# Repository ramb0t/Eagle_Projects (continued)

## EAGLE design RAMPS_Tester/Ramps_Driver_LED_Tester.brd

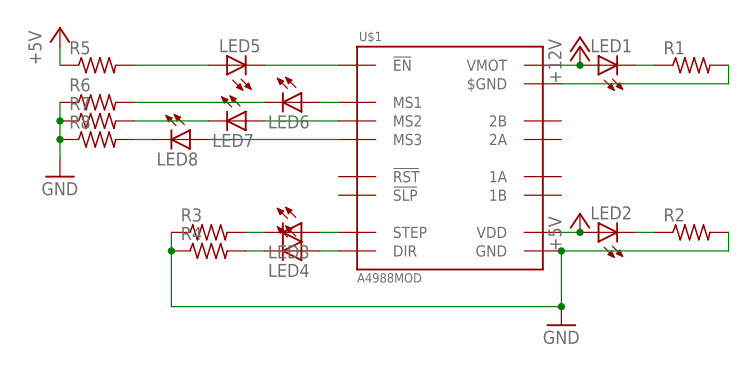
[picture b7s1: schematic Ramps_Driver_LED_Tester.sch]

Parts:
LED1, LED2, LED3, LED4, LED5, LED6, LED7, LED8: LEDCHIPLED_0805; CHIPLED_0805
R1, R2, R3, R4, R5, R6, R7, R8: R-US_R0805; R0805
U$1: A4988MOD

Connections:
+5V: LED2.A, R5.1, U$1.P$10 (VDD)
+12V: LED1.A, U$1.P$16 (VMOT)
GND: R2.2, R3.1, R4.1, R6.1, R7.1, R8.1, U$1.P$9 (GND)
unnamed: LED1.C, R1.1
unnamed: LED2.C, R2.1
unnamed: LED3.A, U$1.P$7 (STEP)
unnamed: LED4.A, U$1.P$8 (DIR)
unnamed: LED3.C, R3.2
unnamed: LED4.C, R4.2
unnamed: LED5.C, U$1.P$1 (!EN)
unnamed: LED5.A, R5.2
unnamed: LED6.A, U$1.P$2 (MS1)
unnamed: LED8.A, U$1.P$4 (MS3)
unnamed: LED7.A, U$1.P$3 (MS2)
unnamed: LED6.C, R6.2
unnamed: LED7.C, R7.2
unnamed: LED8.C, R8.2
unnamed: R1.2, U$1.P$15 ($GND)

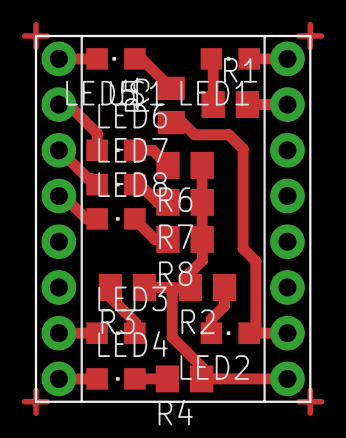
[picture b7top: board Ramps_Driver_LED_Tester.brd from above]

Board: 2 copper layers, 15.2 x 20.3 mm, 17 parts (0 on the bottom side), 18 nets.

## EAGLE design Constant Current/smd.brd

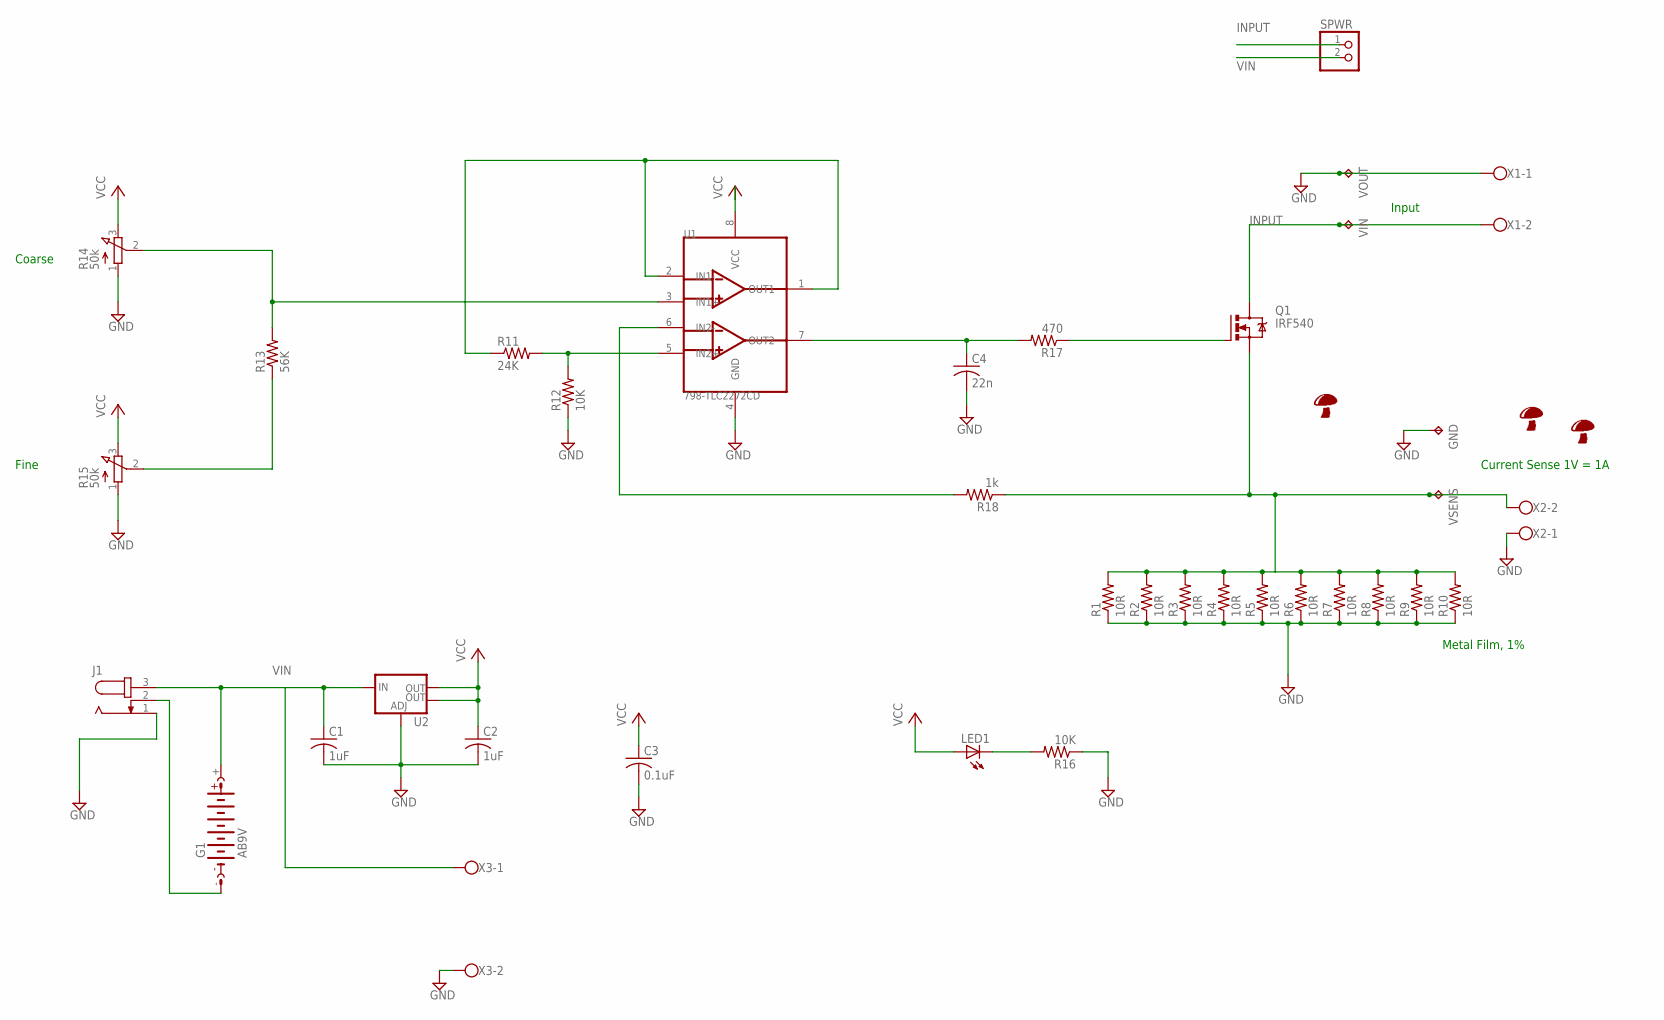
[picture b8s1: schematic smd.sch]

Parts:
C1, C2: 1uF; C0805
C3: 0.1uF; C0805
C4: 22n; C0805
G1: AB9V
GND: TPPAD1-13Y; P1-13Y
J1: JACK-PLUG0; SPC4077
LED1: LEDCHIP-LED0805; CHIP-LED0805
Q1: IRF540; TO220BV
R1, R2, R3, R4, R5, R6, R7, R8, R9, R10: 10R; R2512
R11: 24K; M0805
R12, R16: 10K; M0805
R13: 56K; M0805
R14, R15: 50k; 3RP/1610N
R17: 470; M0805
R18: 1k; M0805
SPWR: PINHD-1X2; 1X02
U1: 798-TLC2272CD; ANDREW/B6D66
U2: V_REG_LM1117SOT223; SOT223
U$1: SHROOM5MM; SHROOM
U$2: SHROOM10MM
U$3: SHROOMTOPSILK; SHROOM_TS
VIN: TPPAD1-13Y; P1-13Y
VOUT: TPPAD1-13Y; P1-13Y
VSENS: TPPAD1-13Y; P1-13Y
X1, X2, X3: W237-102

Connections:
AUXIN: G1.-, J1.2
GND: C1.2, C2.2, C3.2, C4.2, GND.TP, J1.1, R1.1, R2.1, R3.1, R4.1, R5.1, R6.1, R7.1, R8.1, R9.1, R10.1, R12.1, R14.1 (A), R15.1 (A), R16.1, U1.4 (GND), U2.1 (ADJ), VOUT.TP, X1.1, X2.1, X3.2
INPUT: Q1.D, SPWR.1, VIN.TP, X1.2
unnamed: Q1.S, R1.2, R2.2, R3.2, R4.2, R5.2, R6.2, R7.2, R8.2, R9.2, R10.2, R18.1, VSENS.TP, X2.2
unnamed: R18.2, U1.6 (IN2-)
unnamed: R11.1, U1.1 (OUT1), U1.2 (IN1-)
unnamed: R11.2, R12.2, U1.5 (IN2+)
unnamed: R13.2, R14.2 (S), U1.3 (IN1+)
unnamed: R13.1, R15.2 (S)
unnamed: LED1.C, R16.2
unnamed: C4.1, R17.2, U1.7 (OUT2)
unnamed: Q1.G, R17.1
VCC: C2.1, C3.1, LED1.A, R14.3 (E), R15.3 (E), U1.8 (VCC), U2.2 (OUT), U2.4 (OUT)
VIN: C1.1, G1.+, J1.3, SPWR.2, U2.3 (IN), X3.1

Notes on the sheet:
Input
Current Sense 1V = 1A
Metal Film, 1%
Coarse
Fine

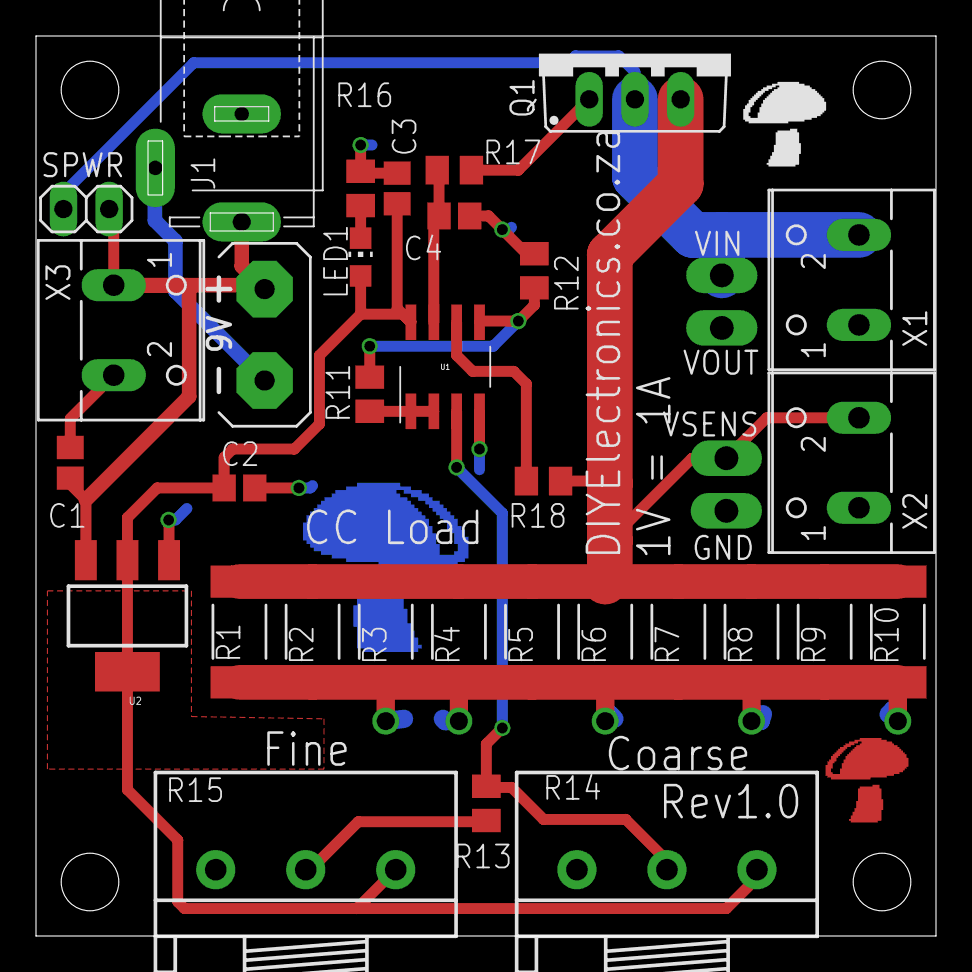
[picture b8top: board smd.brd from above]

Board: 2 copper layers, 50.0 x 50.0 mm, 39 parts (1 on the bottom side), 14 nets.

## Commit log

2015-06-28 First Commit Trying to get stuff up on SC!
2015-06-29 Worked on fan controller a bit..
2015-06-29 Just learing about terminal commands...
2015-09-03 added some new stuff...
2015-09-17 Small change to my DRU
2016-03-09 LoRa Breakout..
2016-03-09 Camera Slider board, AL V1.1 and others
2016-03-09 Updated cameraslider
2016-03-23 Working on constant current load :)
2016-04-08 Tidy up after making boards
2016-05-10 Working on cameraslider, dev code time
2016-05-13 Sent for manufacture :)
2016-05-13 Ramps tester V1 done :)
2016-05-15 Made a bigger panel..
2016-05-17 Messin with the code
2016-05-18 Working on RAMPS UPS
2016-06-01 Updates...
2016-06-03 Working on mag switch
2016-06-07 MagSwitch ready to prototype!
2016-06-07 Updated text
2016-06-18 magswitch update
2016-06-21 Working on camera slider
2016-06-22 Messing arround with IDEs ... PlatformIO looks cool!
2016-10-25 Magswitch Revision
2016-11-10 CameraSliderFirmware dev
2016-12-04 Got speed working
2016-12-04 Enstops and intterupts working
2017-01-22 Camera Slider dev
    Working on calibration procedure
2017-01-23 Still working on calibration. Need to refactor
2017-01-23 Starting to split into multiple files
2017-01-23 Added extern vars
2017-01-23 Saved changes...
2017-01-23 Compiling again
2017-01-23 Split encoder code out
2017-01-23 Added encoder result back
2017-01-23 Changed calibration function
2017-01-23 Fixed debug code
2017-01-24 Calib improvments
2017-01-24 Breaking things getting the oled code split out
2017-01-25 Oled working :)
2017-01-25 Moved camera slider into own repo
2017-03-29 Ordered new AL boards
2017-05-09 DIY version of the MK42
2017-05-09 Auto stash before merge of "master" and "origin/master"
2017-05-09 Ready for heatbed production?
2017-08-31 Moved Auto_Level to DIYElectronicsZA
2017-08-31 Clean Up :)
2019-03-27 Started MS SC
2019-04-01 Added Digipot
2019-04-01 Improved Board to V2.1
2019-04-03 Working on MS electron
2019-04-04 More MS dev
2019-04-05 Added Isolated CANBUS etc
2019-04-05 Added datasheets etc
2019-04-07 Neatened Schematic
2019-04-07 Layout started
2019-04-08 Layout Almost Done
2019-04-09 Almost done layout MS
2019-04-12 tweaks
2019-04-14 Removed MS files
